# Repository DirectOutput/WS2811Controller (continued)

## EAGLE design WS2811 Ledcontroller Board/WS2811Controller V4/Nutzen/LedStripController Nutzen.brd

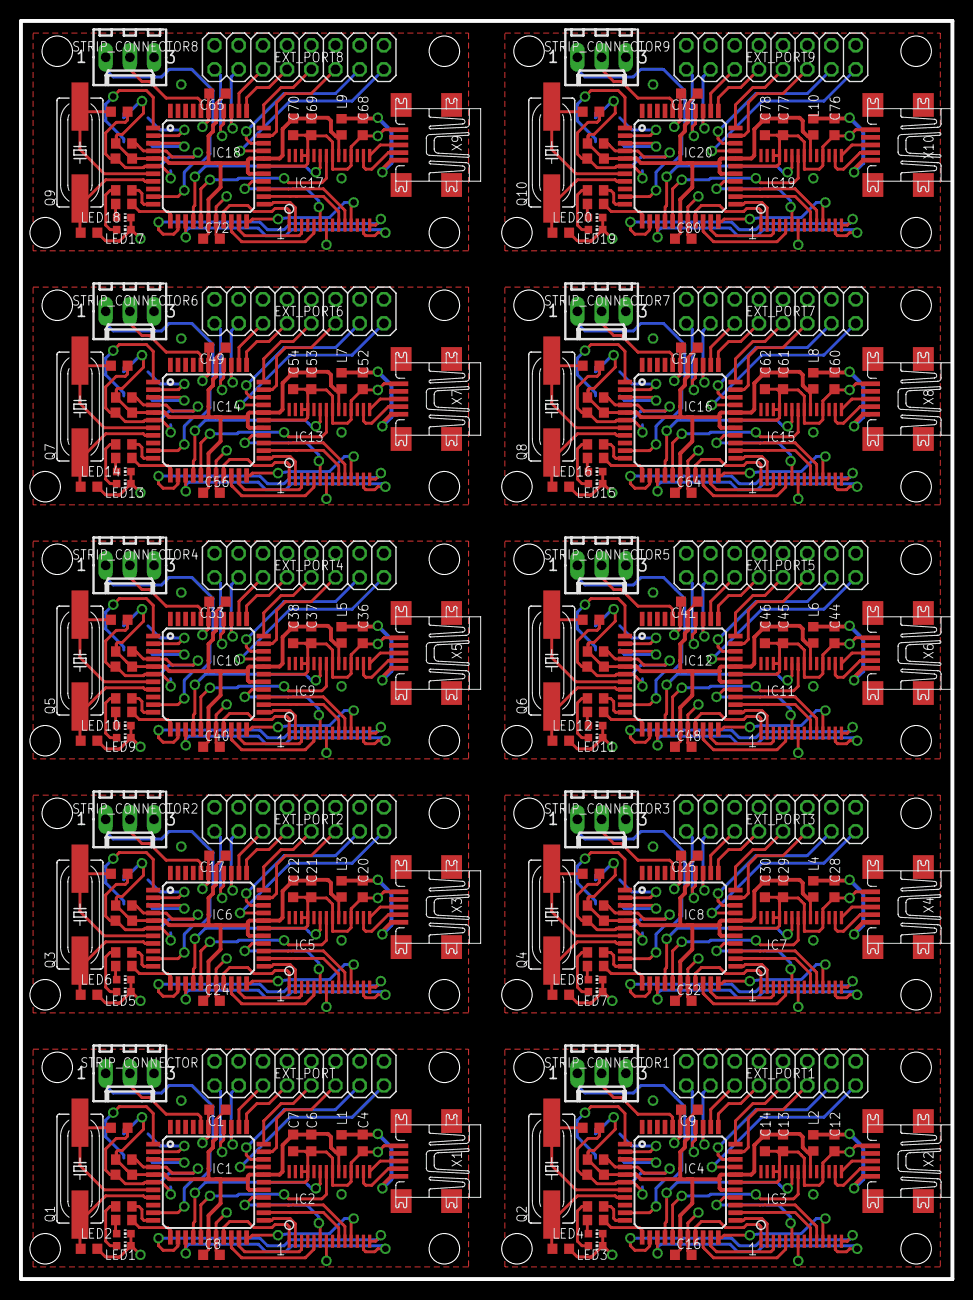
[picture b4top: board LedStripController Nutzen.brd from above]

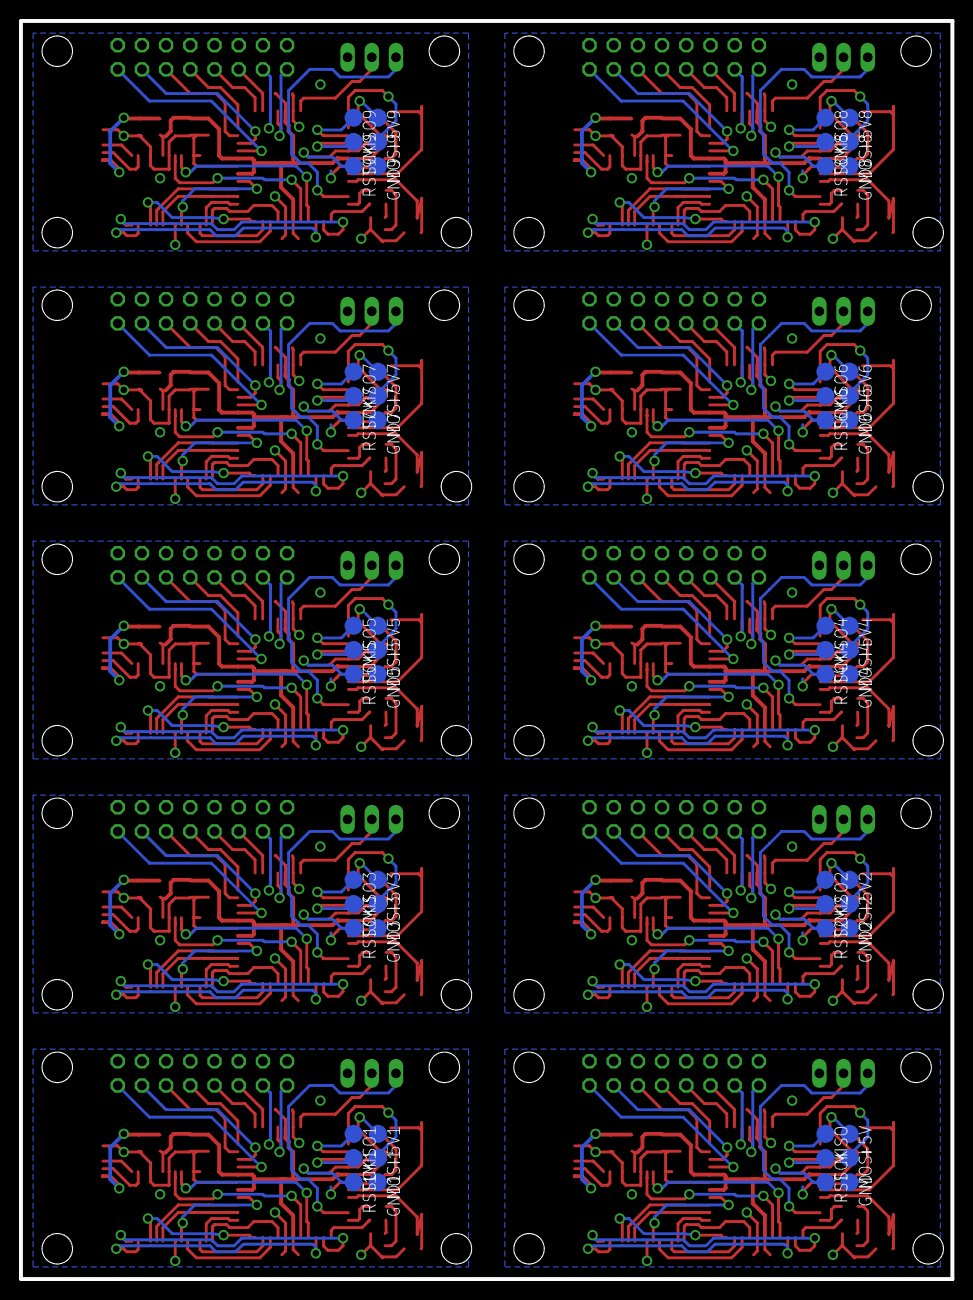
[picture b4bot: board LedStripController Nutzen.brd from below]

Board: 2 copper layers, 97.8 x 132.1 mm, 265 parts (60 on the bottom side), 370 nets.

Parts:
+5V, +5V1, +5V2, +5V3, +5V4, +5V5, +5V6, +5V7, +5V8, +5V9: TP19R
C1, C5, C6, C8, C9, C13, C15, C16, C17, C21, C23, C24, C25, C29, C31, C32, C33, C37, C39, C40, C41, C45, C47, C48, C49, C53, C55, C56, C57, C61, C63, C64, C65, C69, C71, C72, C73, C77, C79, C80: 100nF; C0603K
C2, C3, C10, C11, C18, C19, C26, C27, C34, C35, C42, C43, C50, C51, C58, C59, C66, C67, C74, C75: 22pf; C0603K
C4, C12, C20, C28, C36, C44, C52, C60, C68, C76: 10n; C0603K
C7, C14, C22, C30, C38, C46, C54, C62, C70, C78: 10uf; C0603K
E$1, E$2, E$3, E$4, E$5: DOUBLE_LIZARD_SMALL
EXT_PORT, EXT_PORT1, EXT_PORT2, EXT_PORT3, EXT_PORT4, EXT_PORT5, EXT_PORT6, EXT_PORT7, EXT_PORT8, EXT_PORT9: 2X08
GND, GND1, GND2, GND3, GND4, GND5, GND6, GND7, GND8, GND9: TP19R
IC1, IC4, IC6, IC8, IC10, IC12, IC14, IC16, IC18, IC20: MEGA1284; TQFP44
IC2, IC3, IC5, IC7, IC9, IC11, IC13, IC15, IC17, IC19: FT245RL; SSOP28DB
L1, L2, L3, L4, L5, L6, L7, L8, L9, L10: 1.5A/307; R0603
LED1, LED2, LED3, LED4, LED5, LED6, LED7, LED8, LED9, LED10, LED11, LED12, LED13, LED14, LED15, LED16, LED17, LED18, LED19, LED20: CHIP-LED0603
MISO, MISO1, MISO2, MISO3, MISO4, MISO5, MISO6, MISO7, MISO8, MISO9: TP19R
MOSI, MOSI1, MOSI2, MOSI3, MOSI4, MOSI5, MOSI6, MOSI7, MOSI8, MOSI9: TP19R
Q1, Q2, Q3, Q4, Q5, Q6, Q7, Q8, Q9, Q10: 20Mhz; SM49
R1, R4, R7, R10, R13, R16, R19, R22, R25, R28: 10k; R0603
R2, R3, R5, R6, R8, R9, R11, R12, R14, R15, R17, R18, R20, R21, R23, R24, R26, R27, R29, R30: 330; R0603
RST, RST1, RST2, RST3, RST4, RST5, RST6, RST7, RST8, RST9: TP19R
SCK, SCK1, SCK2, SCK3, SCK4, SCK5, SCK6, SCK7, SCK8, SCK9: TP19R
STRIP_CONNECTOR, STRIP_CONNECTOR1, STRIP_CONNECTOR2, STRIP_CONNECTOR3, STRIP_CONNECTOR4, STRIP_CONNECTOR5, STRIP_CONNECTOR6, STRIP_CONNECTOR7, STRIP_CONNECTOR8, STRIP_CONNECTOR9: 6410-03
X1, X2, X3, X4, X5, X6, X7, X8, X9, X10: MINI-USB-UX60A-MB-5ST; UX60A-MB-5ST

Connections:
+5V: +5V.TP, C1.1, C5.1, C6.1, C7.1, C8.1, IC1.5, IC1.17, IC1.27, IC1.29, IC1.38, IC2.20, L1.2, R1.1
+5V1: +5V1.TP, C9.1, C13.1, C14.1, C15.1, C16.1, IC3.20, IC4.5, IC4.17, IC4.27, IC4.29, IC4.38, L2.2, R4.1
+5V2: +5V2.TP, C17.1, C21.1, C22.1, C23.1, C24.1, IC5.20, IC6.5, IC6.17, IC6.27, IC6.29, IC6.38, L3.2, R7.1
+5V3: +5V3.TP, C25.1, C29.1, C30.1, C31.1, C32.1, IC7.20, IC8.5, IC8.17, IC8.27, IC8.29, IC8.38, L4.2, R10.1
+5V4: +5V4.TP, C33.1, C37.1, C38.1, C39.1, C40.1, IC9.20, IC10.5, IC10.17, IC10.27, IC10.29, IC10.38, L5.2, R13.1
+5V5: +5V5.TP, C41.1, C45.1, C46.1, C47.1, C48.1, IC11.20, IC12.5, IC12.17, IC12.27, IC12.29, IC12.38, L6.2, R16.1
+5V6: +5V6.TP, C49.1, C53.1, C54.1, C55.1, C56.1, IC13.20, IC14.5, IC14.17, IC14.27, IC14.29, IC14.38, L7.2, R19.1
+5V7: +5V7.TP, C57.1, C61.1, C62.1, C63.1, C64.1, IC15.20, IC16.5, IC16.17, IC16.27, IC16.29, IC16.38, L8.2, R22.1
+5V8: +5V8.TP, C65.1, C69.1, C70.1, C71.1, C72.1, IC17.20, IC18.5, IC18.17, IC18.27, IC18.29, IC18.38, L9.2, R25.1
+5V9: +5V9.TP, C73.1, C77.1, C78.1, C79.1, C80.1, IC19.20, IC20.5, IC20.17, IC20.27, IC20.29, IC20.38, L10.2, R28.1
CLOCK: IC1.40, STRIP_CONNECTOR.2
CLOCK1: IC4.40, STRIP_CONNECTOR1.2
CLOCK2: IC6.40, STRIP_CONNECTOR2.2
CLOCK3: IC8.40, STRIP_CONNECTOR3.2
CLOCK4: IC10.40, STRIP_CONNECTOR4.2
CLOCK5: IC12.40, STRIP_CONNECTOR5.2
CLOCK6: IC14.40, STRIP_CONNECTOR6.2
CLOCK7: IC16.40, STRIP_CONNECTOR7.2
CLOCK8: IC18.40, STRIP_CONNECTOR8.2
CLOCK9: IC20.40, STRIP_CONNECTOR9.2
D0: IC1.19, IC2.1
D1: IC1.20, IC2.5
D2: IC1.21, IC2.3
D3: IC1.22, IC2.11
D4: IC1.23, IC2.2
D5: IC1.24, IC2.9
D6: IC1.25, IC2.10
D7: IC1.26, IC2.6
D8: IC3.1, IC4.19
D9: IC3.5, IC4.20
D10: IC3.3, IC4.21
D11: IC3.11, IC4.22
D12: IC3.2, IC4.23
D13: IC3.10, IC4.25
D14: IC3.6, IC4.26
D15: IC3.9, IC4.24
D16: IC5.1, IC6.19
D17: IC5.5, IC6.20
D18: IC5.3, IC6.21
D19: IC5.11, IC6.22
D20: IC5.2, IC6.23
D21: IC5.10, IC6.25
D22: IC5.6, IC6.26
D23: IC5.9, IC6.24
D24: IC7.1, IC8.19
D25: IC7.5, IC8.20
D26: IC7.3, IC8.21
D27: IC7.11, IC8.22
D28: IC7.2, IC8.23
D29: IC7.10, IC8.25
D30: IC7.6, IC8.26
D31: IC7.9, IC8.24
D32: IC9.1, IC10.19
D33: IC9.5, IC10.20
D34: IC9.3, IC10.21
D35: IC9.11, IC10.22
D36: IC9.2, IC10.23
D37: IC9.10, IC10.25
D38: IC9.6, IC10.26
D39: IC9.9, IC10.24
D40: IC11.1, IC12.19
D41: IC11.5, IC12.20
D42: IC11.3, IC12.21
D43: IC11.11, IC12.22
D44: IC11.2, IC12.23
D45: IC11.10, IC12.25
D46: IC11.6, IC12.26
D47: IC11.9, IC12.24
D48: IC13.1, IC14.19
D49: IC13.5, IC14.20
D50: IC13.3, IC14.21
D51: IC13.11, IC14.22
D52: IC13.2, IC14.23
D53: IC13.10, IC14.25
D54: IC13.6, IC14.26
D55: IC13.9, IC14.24
D56: IC15.1, IC16.19
D57: IC15.5, IC16.20
D58: IC15.3, IC16.21
D59: IC15.11, IC16.22
D60: IC15.2, IC16.23
D61: IC15.10, IC16.25
D62: IC15.6, IC16.26
D63: IC15.9, IC16.24
D64: IC17.1, IC18.19
D65: IC17.5, IC18.20
D66: IC17.3, IC18.21
D67: IC17.11, IC18.22
D68: IC17.2, IC18.23
D69: IC17.10, IC18.25
D70: IC17.6, IC18.26
D71: IC17.9, IC18.24
D72: IC19.1, IC20.19
D73: IC19.5, IC20.20
D74: IC19.3, IC20.21
D75: IC19.11, IC20.22
D76: IC19.2, IC20.23
D77: IC19.10, IC20.25
D78: IC19.6, IC20.26
D79: IC19.9, IC20.24
D+: IC2.15, X1.3
D+1: IC3.15, X2.3
D+2: IC5.15, X3.3
D+3: IC7.15, X4.3
D+4: IC9.15, X5.3
D+5: IC11.15, X6.3
D+6: IC13.15, X7.3
D+7: IC15.15, X8.3
D+8: IC17.15, X9.3
D+9: IC19.15, X10.3
D-: IC2.16, X1.2
D-1: IC3.16, X2.2
D-2: IC5.16, X3.2
D-3: IC7.16, X4.2
D-4: IC9.16, X5.2
D-5: IC11.16, X6.2
D-6: IC13.16, X7.2
D-7: IC15.16, X8.2
D-8: IC17.16, X9.2
D-9: IC19.16, X10.2
DATA: IC1.10, STRIP_CONNECTOR.1
DATA1: IC4.10, STRIP_CONNECTOR1.1
DATA2: IC6.10, STRIP_CONNECTOR2.1
DATA3: IC8.10, STRIP_CONNECTOR3.1
DATA4: IC10.10, STRIP_CONNECTOR4.1
DATA5: IC12.10, STRIP_CONNECTOR5.1
DATA6: IC14.10, STRIP_CONNECTOR6.1
DATA7: IC16.10, STRIP_CONNECTOR7.1
DATA8: IC18.10, STRIP_CONNECTOR8.1
DATA9: IC20.10, STRIP_CONNECTOR9.1
GND: C1.2, C2.1, C3.1, C4.2, C5.2, C6.2, C7.2, C8.2, EXT_PORT.2, EXT_PORT.4, EXT_PORT.6, EXT_PORT.8, EXT_PORT.10, EXT_PORT.12, EXT_PORT.14, EXT_PORT.16, GND.TP, IC1.6, IC1.18, IC1.28, IC1.39, IC2.7, IC2.18, IC2.21, IC2.25, IC2.26, LED1.C, LED2.C, STRIP_CONNECTOR.3, X1.5
GND1: C9.2, C10.1, C11.1, C12.2, C13.2, C14.2, C15.2, C16.2, EXT_PORT1.2, EXT_PORT1.4, EXT_PORT1.6, EXT_PORT1.8, EXT_PORT1.10, EXT_PORT1.12, EXT_PORT1.14, EXT_PORT1.16, GND1.TP, IC3.7, IC3.18, IC3.21, IC3.25, IC3.26, IC4.6, IC4.18, IC4.28, IC4.39, LED3.C, LED4.C, STRIP_CONNECTOR1.3, X2.5
GND2: C17.2, C18.1, C19.1, C20.2, C21.2, C22.2, C23.2, C24.2, EXT_PORT2.2, EXT_PORT2.4, EXT_PORT2.6, EXT_PORT2.8, EXT_PORT2.10, EXT_PORT2.12, EXT_PORT2.14, EXT_PORT2.16, GND2.TP, IC5.7, IC5.18, IC5.21, IC5.25, IC5.26, IC6.6, IC6.18, IC6.28, IC6.39, LED5.C, LED6.C, STRIP_CONNECTOR2.3, X3.5
GND3: C25.2, C26.1, C27.1, C28.2, C29.2, C30.2, C31.2, C32.2, EXT_PORT3.2, EXT_PORT3.4, EXT_PORT3.6, EXT_PORT3.8, EXT_PORT3.10, EXT_PORT3.12, EXT_PORT3.14, EXT_PORT3.16, GND3.TP, IC7.7, IC7.18, IC7.21, IC7.25, IC7.26, IC8.6, IC8.18, IC8.28, IC8.39, LED7.C, LED8.C, STRIP_CONNECTOR3.3, X4.5
GND4: C33.2, C34.1, C35.1, C36.2, C37.2, C38.2, C39.2, C40.2, EXT_PORT4.2, EXT_PORT4.4, EXT_PORT4.6, EXT_PORT4.8, EXT_PORT4.10, EXT_PORT4.12, EXT_PORT4.14, EXT_PORT4.16, GND4.TP, IC9.7, IC9.18, IC9.21, IC9.25, IC9.26, IC10.6, IC10.18, IC10.28, IC10.39, LED9.C, LED10.C, STRIP_CONNECTOR4.3, X5.5
GND5: C41.2, C42.1, C43.1, C44.2, C45.2, C46.2, C47.2, C48.2, EXT_PORT5.2, EXT_PORT5.4, EXT_PORT5.6, EXT_PORT5.8, EXT_PORT5.10, EXT_PORT5.12, EXT_PORT5.14, EXT_PORT5.16, GND5.TP, IC11.7, IC11.18, IC11.21, IC11.25, IC11.26, IC12.6, IC12.18, IC12.28, IC12.39, LED11.C, LED12.C, STRIP_CONNECTOR5.3, X6.5
GND6: C49.2, C50.1, C51.1, C52.2, C53.2, C54.2, C55.2, C56.2, EXT_PORT6.2, EXT_PORT6.4, EXT_PORT6.6, EXT_PORT6.8, EXT_PORT6.10, EXT_PORT6.12, EXT_PORT6.14, EXT_PORT6.16, GND6.TP, IC13.7, IC13.18, IC13.21, IC13.25, IC13.26, IC14.6, IC14.18, IC14.28, IC14.39, LED13.C, LED14.C, STRIP_CONNECTOR6.3, X7.5
GND7: C57.2, C58.1, C59.1, C60.2, C61.2, C62.2, C63.2, C64.2, EXT_PORT7.2, EXT_PORT7.4, EXT_PORT7.6, EXT_PORT7.8, EXT_PORT7.10, EXT_PORT7.12, EXT_PORT7.14, EXT_PORT7.16, GND7.TP, IC15.7, IC15.18, IC15.21, IC15.25, IC15.26, IC16.6, IC16.18, IC16.28, IC16.39, LED15.C, LED16.C, STRIP_CONNECTOR7.3, X8.5
GND8: C65.2, C66.1, C67.1, C68.2, C69.2, C70.2, C71.2, C72.2, EXT_PORT8.2, EXT_PORT8.4, EXT_PORT8.6, EXT_PORT8.8, EXT_PORT8.10, EXT_PORT8.12, EXT_PORT8.14, EXT_PORT8.16, GND8.TP, IC17.7, IC17.18, IC17.21, IC17.25, IC17.26, IC18.6, IC18.18, IC18.28, IC18.39, LED17.C, LED18.C, STRIP_CONNECTOR8.3, X9.5
GND9: C73.2, C74.1, C75.1, C76.2, C77.2, C78.2, C79.2, C80.2, EXT_PORT9.2, EXT_PORT9.4, EXT_PORT9.6, EXT_PORT9.8, EXT_PORT9.10, EXT_PORT9.12, EXT_PORT9.14, EXT_PORT9.16, GND9.TP, IC19.7, IC19.18, IC19.21, IC19.25, IC19.26, IC20.6, IC20.18, IC20.28, IC20.39, LED19.C, LED20.C, STRIP_CONNECTOR9.3, X10.5
MISO: IC1.2, MISO.TP
MISO1: IC4.2, MISO1.TP
MISO2: IC6.2, MISO2.TP
MISO3: IC8.2, MISO3.TP
MISO4: IC10.2, MISO4.TP
MISO5: IC12.2, MISO5.TP
MISO6: IC14.2, MISO6.TP
MISO7: IC16.2, MISO7.TP
MISO8: IC18.2, MISO8.TP
MISO9: IC20.2, MISO9.TP
MOSI: IC1.1, MOSI.TP
MOSI1: IC4.1, MOSI1.TP
MOSI2: IC6.1, MOSI2.TP
MOSI3: IC8.1, MOSI3.TP
MOSI4: IC10.1, MOSI4.TP
MOSI5: IC12.1, MOSI5.TP
MOSI6: IC14.1, MOSI6.TP
MOSI7: IC16.1, MOSI7.TP
MOSI8: IC18.1, MOSI8.TP
MOSI9: IC20.1, MOSI9.TP
unnamed: EXT_PORT.15, IC1.30
unnamed: EXT_PORT.13, IC1.31
unnamed: IC1.11, R2.1
unnamed: EXT_PORT.11, IC1.32
unnamed: EXT_PORT.9, IC1.33
unnamed: IC1.12, R3.1
unnamed: EXT_PORT.7, IC1.34
unnamed: C2.2, IC1.8, Q1.1
unnamed: C3.2, IC1.7, Q1.2
unnamed: EXT_PORT.5, IC1.35
unnamed: EXT_PORT.3, IC1.36
unnamed: C10.2, IC4.8, Q2.1
unnamed: EXT_PORT.1, IC1.37
unnamed: C11.2, IC4.7, Q2.2
unnamed: LED3.A, R5.2
unnamed: LED4.A, R6.2
unnamed: EXT_PORT1.15, IC4.30
unnamed: EXT_PORT1.13, IC4.31
unnamed: EXT_PORT1.11, IC4.32
unnamed: EXT_PORT1.9, IC4.33
unnamed: LED1.A, R2.2
unnamed: LED2.A, R3.2
unnamed: EXT_PORT1.7, IC4.34
unnamed: EXT_PORT1.5, IC4.35
unnamed: EXT_PORT1.3, IC4.36
unnamed: EXT_PORT1.1, IC4.37
unnamed: IC4.11, R5.1
unnamed: IC4.12, R6.1
unnamed: C18.2, IC6.8, Q3.1
unnamed: C19.2, IC6.7, Q3.2
unnamed: LED5.A, R8.2
unnamed: LED6.A, R9.2
unnamed: EXT_PORT2.15, IC6.30
unnamed: EXT_PORT2.13, IC6.31
unnamed: EXT_PORT2.11, IC6.32
unnamed: EXT_PORT2.9, IC6.33
unnamed: EXT_PORT2.7, IC6.34
unnamed: EXT_PORT2.5, IC6.35
unnamed: EXT_PORT2.3, IC6.36
unnamed: EXT_PORT2.1, IC6.37
unnamed: IC6.11, R8.1
unnamed: IC6.12, R9.1
unnamed: C26.2, IC8.8, Q4.1
unnamed: C27.2, IC8.7, Q4.2
unnamed: LED7.A, R11.2
unnamed: LED8.A, R12.2
unnamed: EXT_PORT3.15, IC8.30
unnamed: EXT_PORT3.13, IC8.31
unnamed: EXT_PORT3.11, IC8.32
unnamed: EXT_PORT3.9, IC8.33
unnamed: EXT_PORT3.7, IC8.34
unnamed: EXT_PORT3.5, IC8.35
unnamed: EXT_PORT3.3, IC8.36
unnamed: EXT_PORT3.1, IC8.37
unnamed: IC8.11, R11.1
unnamed: IC8.12, R12.1
unnamed: C34.2, IC10.8, Q5.1
unnamed: C35.2, IC10.7, Q5.2
unnamed: LED9.A, R14.2
unnamed: LED10.A, R15.2
unnamed: EXT_PORT4.15, IC10.30
unnamed: EXT_PORT4.13, IC10.31
unnamed: EXT_PORT4.11, IC10.32
unnamed: EXT_PORT4.9, IC10.33
unnamed: EXT_PORT4.7, IC10.34
unnamed: EXT_PORT4.5, IC10.35
unnamed: EXT_PORT4.3, IC10.36
unnamed: EXT_PORT4.1, IC10.37
unnamed: IC10.11, R14.1
unnamed: IC10.12, R15.1
unnamed: C42.2, IC12.8, Q6.1
unnamed: C43.2, IC12.7, Q6.2
unnamed: LED11.A, R17.2
unnamed: LED12.A, R18.2
unnamed: EXT_PORT5.15, IC12.30
unnamed: EXT_PORT5.13, IC12.31
unnamed: EXT_PORT5.11, IC12.32
unnamed: EXT_PORT5.9, IC12.33
unnamed: EXT_PORT5.7, IC12.34
unnamed: EXT_PORT5.5, IC12.35
unnamed: EXT_PORT5.3, IC12.36
unnamed: EXT_PORT5.1, IC12.37
unnamed: IC12.11, R17.1
unnamed: IC12.12, R18.1
unnamed: C50.2, IC14.8, Q7.1
unnamed: C51.2, IC14.7, Q7.2
unnamed: LED13.A, R20.2
unnamed: LED14.A, R21.2
unnamed: EXT_PORT6.15, IC14.30
unnamed: EXT_PORT6.13, IC14.31
unnamed: EXT_PORT6.11, IC14.32
unnamed: EXT_PORT6.9, IC14.33
unnamed: EXT_PORT6.7, IC14.34
unnamed: EXT_PORT6.5, IC14.35
unnamed: EXT_PORT6.3, IC14.36
unnamed: EXT_PORT6.1, IC14.37
unnamed: IC14.11, R20.1
unnamed: IC14.12, R21.1
unnamed: C58.2, IC16.8, Q8.1
unnamed: C59.2, IC16.7, Q8.2
unnamed: LED15.A, R23.2
unnamed: LED16.A, R24.2
unnamed: EXT_PORT7.15, IC16.30
unnamed: EXT_PORT7.13, IC16.31
unnamed: EXT_PORT7.11, IC16.32
unnamed: EXT_PORT7.9, IC16.33
unnamed: EXT_PORT7.7, IC16.34
unnamed: EXT_PORT7.5, IC16.35
unnamed: EXT_PORT7.3, IC16.36
unnamed: EXT_PORT7.1, IC16.37
unnamed: IC16.11, R23.1
unnamed: IC16.12, R24.1
unnamed: C66.2, IC18.8, Q9.1
unnamed: C67.2, IC18.7, Q9.2
unnamed: LED17.A, R26.2
unnamed: LED18.A, R27.2
unnamed: EXT_PORT8.15, IC18.30
unnamed: EXT_PORT8.13, IC18.31
unnamed: EXT_PORT8.11, IC18.32
unnamed: EXT_PORT8.9, IC18.33
unnamed: EXT_PORT8.7, IC18.34
unnamed: EXT_PORT8.5, IC18.35
unnamed: EXT_PORT8.3, IC18.36
unnamed: EXT_PORT8.1, IC18.37
unnamed: IC18.11, R26.1
unnamed: IC18.12, R27.1
unnamed: C74.2, IC20.8, Q10.1
unnamed: C75.2, IC20.7, Q10.2
unnamed: LED19.A, R29.2
unnamed: LED20.A, R30.2
unnamed: EXT_PORT9.15, IC20.30
unnamed: EXT_PORT9.13, IC20.31
unnamed: EXT_PORT9.11, IC20.32
unnamed: EXT_PORT9.9, IC20.33
unnamed: EXT_PORT9.7, IC20.34
unnamed: EXT_PORT9.5, IC20.35
unnamed: EXT_PORT9.3, IC20.36
unnamed: EXT_PORT9.1, IC20.37
unnamed: IC20.11, R29.1
unnamed: IC20.12, R30.1
RD: IC1.14, IC2.13
RD1: IC3.13, IC4.14
RD2: IC5.13, IC6.14
RD3: IC7.13, IC8.14
RD4: IC9.13, IC10.14
RD5: IC11.13, IC12.14
RD6: IC13.13, IC14.14
RD7: IC15.13, IC16.14
RD8: IC17.13, IC18.14
RD9: IC19.13, IC20.14
RST: IC1.4, R1.2, RST.TP
RST1: IC4.4, R4.2, RST1.TP
RST2: IC6.4, R7.2, RST2.TP
RST3: IC8.4, R10.2, RST3.TP
RST4: IC10.4, R13.2, RST4.TP
RST5: IC12.4, R16.2, RST5.TP
RST6: IC14.4, R19.2, RST6.TP
RST7: IC16.4, R22.2, RST7.TP
RST8: IC18.4, R25.2, RST8.TP
RST9: IC20.4, R28.2, RST9.TP
RXF: IC1.15, IC2.23
RXF1: IC3.23, IC4.15
RXF2: IC5.23, IC6.15
RXF3: IC7.23, IC8.15
RXF4: IC9.23, IC10.15
RXF5: IC11.23, IC12.15
RXF6: IC13.23, IC14.15
RXF7: IC15.23, IC16.15
RXF8: IC17.23, IC18.15
RXF9: IC19.23, IC20.15
SCK: IC1.3, SCK.TP
SCK1: IC4.3, SCK1.TP
SCK2: IC6.3, SCK2.TP
SCK3: IC8.3, SCK3.TP
SCK4: IC10.3, SCK4.TP
SCK5: IC12.3, SCK5.TP
SCK6: IC14.3, SCK6.TP
SCK7: IC16.3, SCK7.TP
SCK8: IC18.3, SCK8.TP
SCK9: IC20.3, SCK9.TP
TXE: IC1.16, IC2.22
TXE1: IC3.22, IC4.16
TXE2: IC5.22, IC6.16
TXE3: IC7.22, IC8.16
TXE4: IC9.22, IC10.16
TXE5: IC11.22, IC12.16
TXE6: IC13.22, IC14.16
TXE7: IC15.22, IC16.16
TXE8: IC17.22, IC18.16
TXE9: IC19.22, IC20.16
USBSUPPLY: C4.1, L1.1, X1.1
USBSUPPLY1: C12.1, L2.1, X2.1
USBSUPPLY2: C20.1, L3.1, X3.1
USBSUPPLY3: C28.1, L4.1, X4.1
USBSUPPLY4: C36.1, L5.1, X5.1
USBSUPPLY5: C44.1, L6.1, X6.1
USBSUPPLY6: C52.1, L7.1, X7.1
USBSUPPLY7: C60.1, L8.1, X8.1
USBSUPPLY8: C68.1, L9.1, X9.1
USBSUPPLY9: C76.1, L10.1, X10.1
WR: IC1.13, IC2.14
WR1: IC3.14, IC4.13
WR2: IC5.14, IC6.13
WR3: IC7.14, IC8.13
WR4: IC9.14, IC10.13
WR5: IC11.14, IC12.13
WR6: IC13.14, IC14.13
WR7: IC15.14, IC16.13
WR8: IC17.14, IC18.13
WR9: IC19.14, IC20.13

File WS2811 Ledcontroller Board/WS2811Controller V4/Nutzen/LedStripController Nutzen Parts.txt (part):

Partlist

Exported from LedStripController Nutzen.brd at 05.06.2014 10:45:40

EAGLE Version 6.4.0 Copyright (c) 1988-2013 CadSoft

Assembly variant: 

Part             Value                 Package      Library          Position (inch)       Orientation


C1               100nF                 C0603K       rcl              (0.8125 0.7)          R180
C2               22pf                  C0603K       rcl              (0.28125 0.125)       R180
C3               22pf                  C0603K       rcl              (0.40625 0.625)       R180
C4               10n                   C0603K       rcl              (1.4125 0.5625)       R270
C5               100nF                 C0603K       rcl              (0.425 0.43125)       R180
C6               100nF                 C0603K       rcl              (1.2 0.5625)          R270
C7               10uf                  C0603K       rcl              (1.125 0.5625)        R270
C8               100nF                 C0603K       rcl              (0.7875 0.1)          R0
C9               100nF                 C0603K       rcl              (2.7625 0.7)          R180
C10              22pf                  C0603K       rcl              (2.23125 0.125)       R180
C11              22pf                  C0603K       rcl              (2.35625 0.625)       R180
C12              10n                   C0603K       rcl              (3.3625 0.5625)       R270
C13              100nF                 C0603K       rcl              (3.15 0.5625)         R270
C14              10uf                  C0603K       rcl              (3.075 0.5625)        R270
C15              100nF                 C0603K       rcl              (2.375 0.43125)       R180
C16              100nF                 C0603K       rcl              (2.7375 0.1)          R0
C17              100nF                 C0603K       rcl              (0.8125 1.75)         R180
C18              22pf                  C0603K       rcl              (0.28125 1.175)       R180
C19              22pf                  C0603K       rcl              (0.40625 1.675)       R180
C20              10n                   C0603K       rcl              (1.4125 1.6125)       R270
C21              100nF                 C0603K       rcl              (1.2 1.6125)          R270
C22              10uf                  C0603K       rcl              (1.125 1.6125)        R270
C23              100nF                 C0603K       rcl              (0.425 1.48125)       R180
C24              100nF                 C0603K       rcl              (0.7875 1.15)         R0
C25              100nF                 C0603K       rcl              (2.7625 1.75)         R180
C26              22pf                  C0603K       rcl              (2.23125 1.175)       R180
C27              22pf                  C0603K       rcl              (2.35625 1.675)       R180
C28              10n                   C0603K       rcl              (3.3625 1.6125)       R270
C29              100nF                 C0603K       rcl              (3.15 1.6125)         R270
C30              10uf                  C0603K       rcl              (3.075 1.6125)        R270
C31              100nF                 C0603K       rcl              (2.375 1.48125)       R180
C32              100nF                 C0603K       rcl              (2.7375 1.15)         R0
C33              100nF                 C0603K       rcl              (0.8125 2.8)          R180
C34              22pf                  C0603K       rcl              (0.28125 2.225)       R180
C35              22pf                  C0603K       rcl              (0.40625 2.725)       R180
C36              10n                   C0603K       rcl              (1.4125 2.6625)       R270
C37              100nF                 C0603K       rcl              (1.2 2.6625)          R270
C38              10uf                  C0603K       rcl              (1.125 2.6625)        R270
C39              100nF                 C0603K       rcl              (0.425 2.53125)       R180
C40              100nF                 C0603K       rcl              (0.7875 2.2)          R0
C41              100nF                 C0603K       rcl              (2.7625 2.8)          R180
C42              22pf                  C0603K       rcl              (2.23125 2.225)       R180
C43              22pf                  C0603K       rcl              (2.35625 2.725)       R180
C44              10n                   C0603K       rcl              (3.3625 2.6625)       R270
C45              100nF                 C0603K       rcl              (3.15 2.6625)         R270
C46              10uf                  C0603K       rcl              (3.075 2.6625)        R270
C47              100nF                 C0603K       rcl              (2.375 2.53125)       R180
C48              100nF                 C0603K       rcl              (2.7375 2.2)          R0
C49              100nF                 C0603K       rcl              (0.8125 3.85)         R180
C50              22pf                  C0603K       rcl              (0.28125 3.275)       R180
C51              22pf                  C0603K       rcl              (0.40625 3.775)       R180
C52              10n                   C0603K       rcl              (1.4125 3.7125)       R270
C53              100nF                 C0603K       rcl              (1.2 3.7125)          R270
C54              10uf                  C0603K       rcl              (1.125 3.7125)        R270
C55              100nF                 C0603K       rcl              (0.425 3.58125)       R180
C56              100nF                 C0603K       rcl              (0.7875 3.25)         R0
C57              100nF                 C0603K       rcl              (2.7625 3.85)         R180
C58              22pf                  C0603K       rcl              (2.23125 3.275)       R180
C59              22pf                  C0603K       rcl              (2.35625 3.775)       R180
C60              10n                   C0603K       rcl              (3.3625 3.7125)       R270
C61              100nF                 C0603K       rcl              (3.15 3.7125)         R270
C62              10uf                  C0603K       rcl              (3.075 3.7125)        R270
C63              100nF                 C0603K       rcl              (2.375 3.58125)       R180
C64              100nF                 C0603K       rcl              (2.7375 3.25)         R0
C65              100nF                 C0603K       rcl              (0.8125 4.9)          R180
C66              22pf                  C0603K       rcl              (0.28125 4.325)       R180
C67              22pf                  C0603K       rcl              (0.40625 4.825)       R180
C68              10n                   C0603K       rcl              (1.4125 4.7625)       R270
C69              100nF                 C0603K       rcl              (1.2 4.7625)          R270
C70              10uf                  C0603K       rcl              (1.125 4.7625)        R270
C71              100nF                 C0603K       rcl              (0.425 4.63125)       R180
C72              100nF                 C0603K       rcl              (0.7875 4.3)          R0
C73              100nF                 C0603K       rcl              (2.7625 4.9)          R180
C74              22pf                  C0603K       rcl              (2.23125 4.325)       R180
C75              22pf                  C0603K       rcl              (2.35625 4.825)       R180
C76              10n                   C0603K       rcl              (3.3625 4.7625)       R270
C77              100nF                 C0603K       rcl              (3.15 4.7625)         R270
C78              10uf                  C0603K       rcl              (3.075 4.7625)        R270
C79              100nF                 C0603K       rcl              (2.375 4.63125)       R180
C80              100nF                 C0603K       rcl              (2.7375 4.3)          R0

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
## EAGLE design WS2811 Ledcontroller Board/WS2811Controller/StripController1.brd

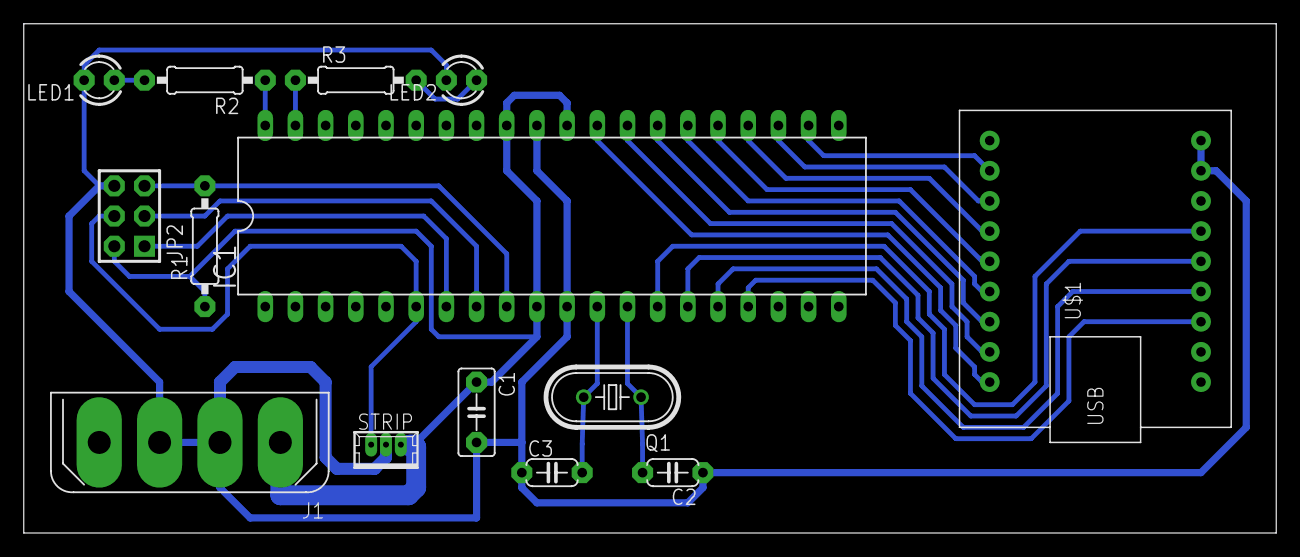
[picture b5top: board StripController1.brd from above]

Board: 2 copper layers, 105.4 x 42.9 mm, 14 parts (0 on the bottom side), 24 nets.

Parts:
C1: 100nF; C050-030X075
C2, C3: 22pf; C050-024X044
IC1: MEGA164P/324P/644P-PU; DIL40
J1: FLOPPY-4
JP2: AVR-ISP-6
LED1, LED2: LED3MM
Q1: 20Mhz; HC49U70
R1: 10k; 0207/10
R2, R3: 330; 0207/10
STRIP: 53047-03
U$1: FT245RL_BREAKOUTBOARD; SPARKFUN_FT245RL_BOARD

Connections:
+5V: C1.1, IC1.10, IC1.30, IC1.32, J1.4, JP2.2, R1.1, STRIP.1
GND: C1.2, C2.1, C3.1, IC1.11, IC1.31, J1.2, J1.3, JP2.6, LED1.K, LED2.K, STRIP.2, U$1.GND1, U$1.GND2
unnamed: IC1.8, JP2.3
unnamed: IC1.7, JP2.1
unnamed: IC1.40, R2.1
unnamed: IC1.9, JP2.5, R1.2
unnamed: IC1.6, JP2.4, STRIP.3
unnamed: IC1.39, R3.1
unnamed: IC1.22, U$1.D0
unnamed: C2.2, IC1.13, Q1.1
unnamed: C3.2, IC1.12, Q1.2
unnamed: IC1.23, U$1.D1
unnamed: IC1.24, U$1.D2
unnamed: IC1.25, U$1.D3
unnamed: IC1.26, U$1.D4
unnamed: IC1.27, U$1.D5
unnamed: IC1.28, U$1.D6
unnamed: IC1.29, U$1.D7
unnamed: IC1.17, U$1.TXE
unnamed: IC1.16, U$1.RXF
unnamed: IC1.14, U$1.RD
unnamed: IC1.15, U$1.WR
unnamed: LED1.A, R2.2
unnamed: LED2.A, R3.2

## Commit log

2023-08-07 Old code uploaded
2023-08-07 Uploaded designs for various versions of the controller board
